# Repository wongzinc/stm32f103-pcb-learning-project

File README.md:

# STM32F103 PCB Learning Project

A custom 2-layer STM32F103C8T6 development board designed in **KiCad 10** as a project-driven introduction to PCB design, component selection, manufacturing preparation, and embedded hardware bring-up.

> **Status:** Rev. 1 PCB design complete. Manufacturing preparation and hardware bring-up in progress.

## Board Preview

| 3D view | Layout |
|---|---|
|  |  |

## Project Goals

I started this project to learn PCB design by building a real microcontroller board rather than only studying individual concepts in isolation.

The goal was to walk the complete hardware workflow end to end:

```
datasheet → schematic → footprint selection → PCB layout
    → BOM / CPL → manufacturing preparation → hardware bring-up
```

## Board Features

| Block | Part |
|---|---|
| MCU | STM32F103C8T6 (LQFP-48) |
| Regulator | AMS1117-3.3 (SOT-223) |
| Clock | 16 MHz HSE crystal + load capacitors |
| Power input | Micro-USB B connector |
| Debug | SWD header |
| Serial | UART header |
| Bus | I²C header |
| Indicator | Status LED |
| Analog supply | Ferrite bead + filter capacitors on VDDA |
| Configuration | BOOT selection switch |
| Stackup | 2-layer, 1.6 mm |

## What I Learned

### 1. A schematic is more than connecting pins

Before this project, PCB design looked like drawing lines between components. Building an STM32 board forced me to work from the datasheet and application notes, and to understand *why* each connection exists.

Pins I had to actually understand rather than just wire up:

- `VDD` / `VSS` — digital power and return
- `VDDA` / `VSSA` — analog power, filtered separately
- `NRST` — reset, with its own RC
- `BOOT0` — boot mode selection at reset
- `OSC_IN` / `OSC_OUT` — HSE crystal
- `SWDIO` / `SWCLK` — debug interface
- UART, I²C, and the USB connector signals

### 2. Power distribution is a system, not a net

The board generates 3.3 V from an AMS1117-3.3. Learning to design around it meant separating concepts I had previously treated as one thing:

- voltage regulation
- bulk capacitance
- local decoupling
- analog supply filtering
- power rails
- ground planes and return paths

The lesson that stuck: a decoupling capacitor is not just "electrically connected" to a power pin. Its **physical placement and current loop are part of the circuit**.

### 3. Capacitors map to frequency, not to a generic "filtering" role

This was the concept that changed how I read schematics. The board uses six different capacitor values, and they are not interchangeable — each one covers a different part of the frequency spectrum.

| Value | Package | Qty | Role |
|---|---|---|---|
| 22 µF | 0805 | 2 | Bulk — regulator input and output reservoir |
| 10 µF | 0603 | 1 | Bulk / rail stabilisation |
| 1 µF | 0402 | 2 | Mid-band, bridges bulk and local decoupling |
| 100 nF | 0402 | 5 | Local decoupling, one per MCU supply pin |
| 10 nF | 0402 | 1 | Analog supply filtering with the ferrite bead |
| 10 pF | 0402 | 2 | Crystal load capacitors — not decoupling at all |

#### Why one value cannot do the whole job

A real capacitor is not just capacitance. It behaves as C in series with **ESR** (resistance) and **ESL** (parasitic inductance from the leads, pads, and internal structure). That series combination has a **self-resonant frequency**:

```
f_SRF = 1 / (2π √(L·C))
```

Below the SRF the part behaves like a capacitor and its impedance falls with frequency. Above the SRF the inductance dominates and impedance *rises* again — the capacitor stops being a capacitor.

Two consequences follow:

- **Larger capacitance → lower SRF.** A 22 µF part is effective in the kHz to low-MHz range and is essentially useless above it.
- **Larger package → higher ESL → lower SRF and a higher impedance floor.** This is why the 100 nF parts are 0402 and not 0805; the package matters as much as the value.

So the values are chosen to overlap. The 22 µF absorbs slow load steps and regulator ripple. The 100 nF supplies the fast current spikes the MCU draws every time its internal logic switches, at tens of MHz, where the bulk capacitor is already inductive.

#### Low-frequency ripple vs high-frequency transients

These are two genuinely different problems:

**Low-frequency ripple** comes from the regulator itself and from slow changes in load current. The AMS1117 is a linear regulator, so there is no switching ripple to filter, but its control loop has finite bandwidth — it cannot respond instantly to a load step. Bulk capacitance covers the gap by acting as a local charge reservoir until the regulator catches up. Here the value is what matters; a few millimetres of trace inductance is negligible at these frequencies.

**High-frequency transients** come from inside the MCU. Every clock edge switches millions of gates, and each switching event draws a short, sharp current pulse. That current has to come from somewhere, and it cannot travel far — at 100 MHz, a few millimetres of trace can contribute more inductance than the capacitor itself. This is why local decoupling is a *layout* problem: the 100 nF has to sit within a few millimetres of its VDD pin, with a short via straight down to the ground plane, so the current loop stays small.

The rule I took away: **large value, near the regulator; small value, near the pin.**

#### One caveat I ran into while reading

The classic advice to parallel a decade spread of values (10 µF ‖ 1 µF ‖ 100 nF) has a known downside — **anti-resonance**. Between two capacitors' SRFs, one is already inductive while the other is still capacitive, and the resulting parallel LC can produce an impedance *peak*. Modern practice often favours several capacitors of the same value over a wide spread. For a learning board at these speeds it does not matter much, but it is worth knowing that the textbook rule is a simplification.

#### Analog supply filtering

`VDDA` gets a ferrite bead (FB1, 120 Ω) plus its own capacitors. The bead is not an inductor in the ideal sense — at high frequency it becomes largely **resistive**, so it dissipates noise energy as heat rather than reflecting it back into the rail. Together with the capacitors it forms a low-pass filter that keeps digital switching noise out of the ADC reference.

#### Crystal load capacitors are a different animal

C10 and C11 (10 pF) are not decoupling. They set the oscillator's load capacitance, which has to match what the crystal specifies:

```
C_L = (C1 × C2) / (C1 + C2) + C_stray
```

Getting these wrong does not cause noise — it shifts the oscillator frequency, or stops it starting at all. `C_stray` includes the PCB traces and the MCU pin capacitance, which is why these traces are kept short.

### 4. Crystal selection is more than a frequency number

Choosing the 16 MHz HSE crystal meant checking:

- package size
- load capacitance (which sets C10/C11 above)
- ESR, against the MCU's oscillator drive capability
- frequency tolerance and temperature drift
- placement — short traces to `OSC_IN` / `OSC_OUT`, guarded from other signals

### 5. SWD, UART and I²C serve different purposes

- **SWD** — programming and debugging, two wires plus reset
- **UART** — asynchronous point-to-point serial
- **I²C** — shared two-wire bus

I²C in particular taught me why `SDA` and `SCL` need pull-up resistors: the bus is **open-drain**, so devices can only pull low. The pull-ups provide the high level, and their value trades rise time against current draw.

### 6. Symbol vs footprint vs physical component

These are three different things, and confusing them is expensive.

- A **schematic symbol** describes the *electrical function* — how many pins and what they do.
- A **footprint** describes the *physical pads and dimensions* on the board.
- The **physical component** is what actually ships.

The naming taught me this the hard way:

```
KiCad footprint:  C_0402_1005Metric

0402  = imperial package code (0.04" × 0.02")
1005  = metric package code  (1.0 mm × 0.5 mm)

Same part. Two measuring systems. One physical size.
```

The trap: metric `0402` is a real and completely different package — 0.4 × 0.2 mm, known as imperial `01005`. A component can have the correct electrical value and still be entirely wrong if the package does not match the footprint on the board.

### 7. Automatic BOM matching cannot be trusted

While preparing the board for assembly, several automatically matched components came back with the wrong package. In one case every 0402 capacitor and resistor had been matched to `01005` parts — six times smaller in area, out of stock, and flagged as high assembly difficulty.

I now verify every line against:

- value
- package / footprint
- voltage or power rating
- tolerance
- dielectric (C0G vs X5R vs X7R) where it matters
- stock availability and whether the part is basic or extended

The connectors, switch, and crystal needed the most attention — for those, matching on a description string is not reliable, and specifying a manufacturer part number is the only dependable approach.

### 8. Layout is an electrical problem

Routing is not about making the ratsnest disappear. During layout I practised:

- component placement driven by signal flow
- trace routing and width
- via placement and count
- ground-plane continuity
- decoupling capacitors close to their pins
- minimising oscillator trace length
- connectors at the board edge
- readable silkscreen
- mechanical mounting holes

I also started thinking about **return-current paths** — the current in the ground plane underneath a trace, rather than just the forward signal.

## Manufacturing Workflow

```
KiCad schematic
      ↓
PCB layout + footprints
      ↓
Gerber / drill files
      ↓
BOM (with manufacturer part numbers)
      ↓
CPL / position file
      ↓
Manufacturer part matching + verification
      ↓
PCB fabrication / assembly
```

## Bring-up Plan

When the board arrives, I plan to validate it in this order — stopping at the first failure rather than powering everything at once:

- [ ] Visual inspection for bridges and misaligned parts
- [ ] Continuity check: 3.3 V to GND, confirm no short
- [ ] Apply input voltage, measure USB / `VBUS`
- [ ] Verify the regulated 3.3 V rail under no load
- [ ] Check rail ripple on a scope
- [ ] Connect ST-Link over SWD
- [ ] Read the MCU device ID
- [ ] Flash a minimal LED blink program
- [ ] Verify HSE oscillator start-up and frequency
- [ ] Test UART loopback
- [ ] Test I²C with a known device
- [ ] Exercise the remaining interfaces

## Planned Rev. 2 Improvements

Rev. 1 is a learning prototype, not a finished design. After bring-up I plan to review:

- component placement and grouping
- routing cleanliness and return paths
- oscillator layout
- USB signal routing and impedance
- footprint selection against real, in-stock parts
- BOM cost and availability
- DFM / DFA considerations
- test-point accessibility
- whether to move from Micro-USB to USB-C

## Repository Layout

```
.
├── pcb_design.kicad_pro
├── pcb_design.kicad_sch
├── pcb_design.kicad_pcb
├── 629105150521_rev1.stp     # 3D model, Micro-USB connector
├── docs/                     # images used in this README
├── manufacturing/            # Gerber, drill, BOM, CPL
└── README.md
```

## Tools

- KiCad 10
- STM32CubeMX
- STM32CubeIDE
- Git / GitHub
- JLCPCB / LCSC

## Project Status

**Revision 1** — PCB design complete, manufacturing preparation in progress.

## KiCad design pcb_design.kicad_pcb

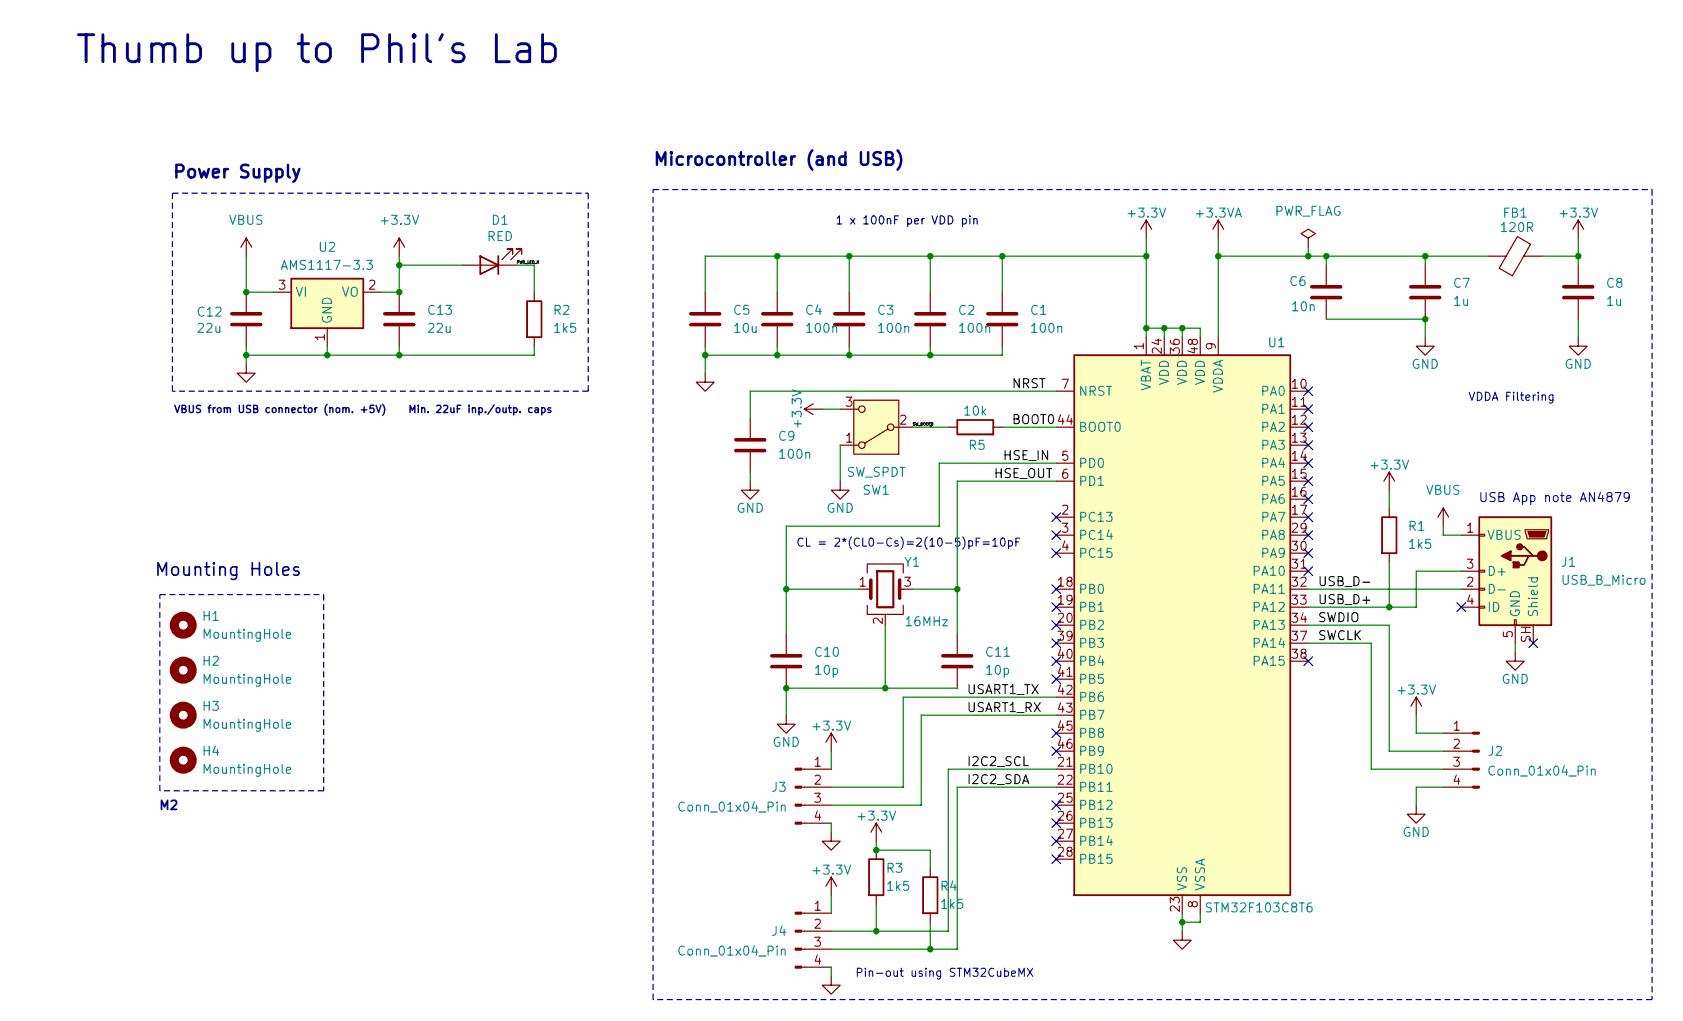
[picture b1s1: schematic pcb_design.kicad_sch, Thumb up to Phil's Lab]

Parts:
C1, C2, C3, C4, C9: 100n; C_0402_1005Metric
C5: 10u; C_0603_1608Metric
C6: 10n; C_0402_1005Metric
C7, C8: 1u; C_0402_1005Metric
C10, C11: 10p; C_0402_1005Metric
C12, C13: 22u; C_0805_2012Metric
D1: RED; LED_0603_1608Metric
FB1: 120R; L_0603_1608Metric
H1, H2, H3, H4: MountingHole; MountingHole_2.2mm_M2
J1: USB_B_Micro; USB_Micro-B_Wuerth_629105150521
J2, J3, J4: Conn_01x04_Pin; PinHeader_1x04_P2.54mm_Vertical
R1, R2, R3, R4: 1k5; R_0402_1005Metric
R5: 10k; R_0402_1005Metric
SW1: SW_SPDT; SW_SPDT_PCM12
U1: STM32F103C8T6; LQFP-48_7x7mm_P0.5mm
U2: AMS1117-3.3; SOT-223-3_TabPin2
Y1: 16MHz; Crystal_SMD_3225-4Pin_3.2x2.5mm

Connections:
+3.3V: C1.1, C2.1, C3.1, C4.1, C5.1, C8.1, C13.1, D1.2 (A), FB1.2, J2.1, J3.1, J4.1, R1.1, R3.1, R4.1, SW1.3 (C), U1.1 (VBAT), U1.24 (VDD), U1.36 (VDD), U1.48 (VDD), U2.2 (VO)
+3.3VA: C6.1, C7.1, FB1.1, U1.9 (VDDA)
/BOOT0: R5.2, U1.44 (BOOT0)
/HSE_IN: C10.1, U1.5 (PD0), Y1.1
/HSE_OUT: C11.1, U1.6 (PD1), Y1.3
/I2C2_SCL: J4.2, R3.2, U1.21 (PB10)
/I2C2_SDA: J4.3, R4.2, U1.22 (PB11)
/NRST: C9.1, U1.7 (NRST)
/PWR_LED_K: D1.1 (K), R2.1
/SWCLK: J2.3, U1.37 (PA14)
/SWDIO: J2.2, U1.34 (PA13)
/SW_BOOT0: R5.1, SW1.2 (B)
/USART1_RX: J3.3, U1.43 (PB7)
/USART1_TX: J3.2, U1.42 (PB6)
/USB_D+: J1.3 (D+), R1.2, U1.33 (PA12)
/USB_D-: J1.2 (D-), U1.32 (PA11)
GND: C1.2, C2.2, C3.2, C4.2, C5.2, C6.2, C7.2, C8.2, C9.2, C10.2, C11.2, C12.2, C13.2, J1.5 (GND), J2.4, J3.4, J4.4, R2.2, SW1.1 (A), U1.8 (VSSA), U1.23 (VSS), U1.35 (VSS), U1.47 (VSS), U2.1 (GND), Y1.2 (G), Y1.4 (G)
VBUS: C12.1, J1.1 (VBUS), U2.3 (VI)

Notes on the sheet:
VBUS from USB connector (nom. +5V) Min. 22uF inp./outp. caps
Microcontroller (and USB)
USB App note AN4879
Mounting Holes
CL = 2*(CL0-Cs)=2(10-5)pF=10pF
Pin-out using STM32CubeMX
Thumb up to Phil's Lab
1 x 100nF per VDD pin
Power Supply
VDDA Filtering

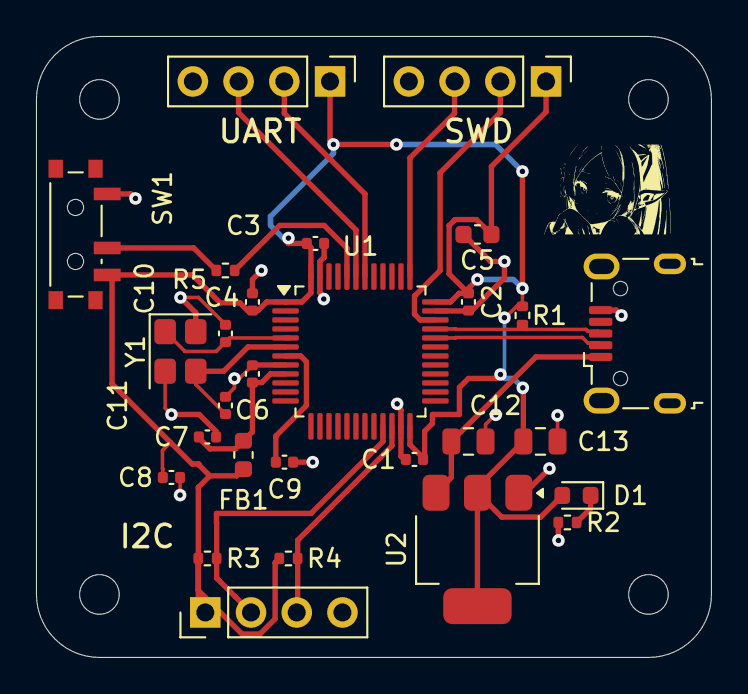
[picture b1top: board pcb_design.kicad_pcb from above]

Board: 2 copper layers, 37.5 x 34.5 mm, 32 parts (0 on the bottom side), 18 nets.

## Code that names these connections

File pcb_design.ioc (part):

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Mcu.Name=STM32F103C(8-B)Tx
Mcu.Package=LQFP48
Mcu.UserName=STM32F103C8Tx
PA11.Mode=Device
PA11.Signal=USB_DM
PA12.Mode=Device
PA12.Signal=USB_DP
PA13.Mode=Serial_Wire
PA13.Signal=SYS_JTMS-SWDIO
PA14.Mode=Serial_Wire
PA14.Signal=SYS_JTCK-SWCLK
PB10.Mode=I2C
PB10.Signal=I2C2_SCL
PB11.Mode=I2C
PB11.Signal=I2C2_SDA
PB6.Mode=Asynchronous
PB6.Signal=USART1_TX
PB7.Mode=Asynchronous
PB7.Signal=USART1_RX
PD0-OSC_IN.Mode=HSE-External-Oscillator
PD0-OSC_IN.Signal=RCC_OSC_IN
PD1-OSC_OUT.Mode=HSE-External-Oscillator
PD1-OSC_OUT.Signal=RCC_OSC_OUT
board=custom
